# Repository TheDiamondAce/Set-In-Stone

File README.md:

# Set In Stone

# Motivation
Starting off with the motivation, I wanted to challenge myself, making something big for my second project, upon which I decided to ultilize my skills of CAD over 2 years on onshape and also my newfound knowledge of C++ hardware coding
I wanted to do a minigame of sorts, learning how modules work and interact with microcontrollers. I realized that most modules use a combination of using eletrical charges to output or input values into code. Which I found to be a revalation suprisingly

# What is this?
This project is a minigame similar to Simon Says and Bop it combined, you have to do multiple inputs to get a point, making it harder and harder as you progress. It is a reaction game of sorts, benefiting the people with great hand to eye coordination

# How to Build?
To build this, you first need to get the pieces as listed in the BOM, you will have to download the code from the Code folder and need to 3D print the enclosure/chassis as well as the button caps. Then, you will need to get the required modules and follow the wiring diagram as shown below here. For the PCB, you will need to first remoe the 3 wires on the left hand of the tft display since you wont need it for the build. Then after you remove it, you will need to solder the modules onto the PCB, however, the parts that you fit to the LID first are the joystick and the display. Then after you connect the PCB to the modules and also to the lid, you will need to get the usb c extension cable and fit it into the usb c gap in the bottom. After, its just a matter of plugging into a power source through the cable, then plug and play!
# What am I proud of?
Most definitely the code first, then the CAD, but not far behind. The reason for this is because I think for the first time, I actually understood the code sorta, and figured out what each thing does, actually using struct functions and enum functions, in an actual way. (Update) Okay, so the first thing I'm proud of now is the PCB as this is the first time i've ever done PCB tinkering, and I'm glad to say, it was a success!
Usually, when I coded, I never really bothered to use such types of functions, but with this project, I realized that, im getting better at coding. For CAD, I really am happy that I managed to get all of the constraints to a precises level to my standards. Also the way I designed it was 
sorta challenging for me at my level.
# What is the next steps?
Im thinking of making it so that there will be more audio and a spritesheet on the display with a mascot, being happy or mad whenever you get something right and wrong. Im also thinking of adding bluetooth audio so that I can implement a simon says mechanic, making it so that on certain cases, you dont press unless the stone says lmao, but not soul says haha.
# Anything else
Nah 
# Ur CAD Diagrams and Wiring?
Oh shoot yeah ur right
# CAD Pictures

## Isometric

## Front

## Back

## Side

# BOM
| Name                                                                                          | Description                                                                           | Quantity | Price  | Why                                                                                        | Link                                                                                                                                                                                                                                                                                                                                                                                                                                                                                                                                                                                                                                |
|-----------------------------------------------------------------------------------------------|---------------------------------------------------------------------------------------|----------|--------|--------------------------------------------------------------------------------------------|-------------------------------------------------------------------------------------------------------------------------------------------------------------------------------------------------------------------------------------------------------------------------------------------------------------------------------------------------------------------------------------------------------------------------------------------------------------------------------------------------------------------------------------------------------------------------------------------------------------------------------------|
| Joystick                                                                                      | A module that uses potentiometers and a stick to measure values                       | 1        | $8.79  | So you can do stuff to memorize for the minigame                                           | https://www.amazon.com/DKARDU-Dual-axis-Joystick-Control-Breakout/dp/B0B5GLYPLT/ref=sr_1_6_sspa?dib=eyJ2IjoiMSJ9.azZ62n4Tl8ZwkrheJyqyCndrP1SV71A4xyAr-iuhJYzian_VPAm1-wcJa1kETLtxM4eNGt-xxm1leb5CyeYzA3nBElRKq_MmfamtrXjfZvH7wPZkzrT96BrQEydKYWCSkKjlWEekTF7VWtR9tcMjoZKWhNFTWNypkJJN8fer6AzldJ-0Q4IYCG_6cRPB-GjUYue5LsoKmklUHP6XbxF4PJ9gZ4sy5qI4osEVQvxmUko.qd12qxOC_v7GZmm8GlitAnJ3g7_pRsO_EVmVD7kz0sU&dib_tag=se&keywords=KY-023&qid=1781695753&sr=8-6-spons&sp_csd=d2lkZ2V0TmFtZT1zcF9tdGY&psc=1                                                                                                                                |
| 12mm Button                                                                                   | A tactile switch that either connects a cirucuit or disconnects depending on input    | 4        | $12.07 | So you can click stuff to memorize for the minigame                                        | https://www.amazon.com/Uxcell-a11111400ux0132-Momentary-Tactile-Button/dp/B0090VQLDK                                                                                                                                                                                                                                                                                                                                                                                                                                                                                                                                                |
| 12mm Button Caps (Red Green Yellow Blue)                                                      | The caps to indentify which button is which (Will be 3D printer most likely)          | 4        | $0.00  | To know which button is which.                                                             | can 3D print through hackclub or by yourself                                                                                                                                                                                                                                                                                                                                                                                                                                                                                                                                                                                        |
| Potentiometer                                                                                 | A module that uses potentiometers and a stick to measure values through rotation      | 1        | $9.99  | Another cool function that gives varation and intresting mechanics                         | https://www.amazon.com/TWTADE-Adjustable-Potentiometer-Resistance-XH2-54-3P/dp/B082FCRQS2/ref=sr_1_11?dib=eyJ2IjoiMSJ9.TaTUlh95QswS_FIIMPYmhtrGpujREngP3Xc1oQRyB9rYfzo5Gjz4PTvWpn5iXK9dcDXyauCQyVTScgKtQiiCgd3LLyPBGxHL-tvGMzznu9_sFYWY9xP6C6awwAKLKjAjD54kWNmqUPUcvBHwoTWNZ5n1v20SmyDv5QPkhg_GJn26vWFLQ7iqdO7V3fx2rxiDINDQcKF5Hye8oN6JiOwa8UQbfrgA9xlyOhBGqnJD3KQ.hsZpGYPSabo9mENvFcCT4852xHdjX3BdothB3Qju_3g&dib_tag=se&keywords=potentiometer&qid=1781262502&sr=8-11&th=1                                                                                                                                                        |
| TFT LCD 2.4 inch ILI9341 Touch                                                                | Display used to show what inputs to press next and as well as score and timer         | 1        | $12.39 | To see what inputs to do next and other data                                               | https://www.amazon.com/ACEIRMC-ILI9341-Display-Touch-240X320/dp/B0C4D5S6G5/ref=sr_1_10_sspa?crid=1KKGFFL8GGC72&dib=eyJ2IjoiMSJ9.aNbS-hCnwROiq-lihDWLj0bSTkExzZcUEg9Thz-MRRtS2XSDTZusdgq0aD1F0WmFP2z1icua7XtMO6m0dMOpn8SqrOFp1HIlcN4kiqw6-RlV7hZO4ruwCns7e_xrwwarWxaiSyrChwiIRUrUY_RlX9OKgmKKALx-gO4lSBbiMaZfKv6a7KsmvzFghX94ueB0tjP9qSX40MXT01v37X8MMYSJqIt6UnkreQ59ftwFdiegDUDVujNbTPq7P3rk02P9OOVeiCEMzoFH8qXlYbO1NNMZsi5VeRhwTNT7sHwGj98.L9Ilfuyvs66CsTIbDNYf3OsazpswS6k4iaS05y2B6dk&dib_tag=se&keywords=ili9341&qid=1781262418&s=electronics&sprefix=ili%2Celectronics%2C409&sr=1-10-spons&sp_csd=d2lkZ2V0TmFtZT1zcF9tdGY&psc=1 |
| -ESP 32                                                                                       | The Microcontroller that will control all functions of the minigame as well as logic. | 1        | $9.99  | To control the whole minigame and logic                                                    | http://amazon.com/HiLetgo-ESP-WROOM-32-Development-Microcontroller-Integrated/dp/B0718T232Z/ref=sr_1_3?crid=1USIEYMJJ17B2&dib=eyJ2IjoiMSJ9.qMJJKscaTbDZH8KOrPXaSvvBOSev_9dSPToXjxjL2hvyn1gBn6UPJN0hkgfCA46MeGIMW0m_k8uVP6ohS8y2Ybx0WAhwI7WeRI7HGIEx1FzRCBDUpYc9OEv48KKiBbsEpRw-msTD6rmtDv4Xvt-FdBguBvBYlMMj4hzZRICsg1IFudiHZVD_F8MFEsmYWqc5av-fzu7UHVx2QYcllMYcUQXPrnJ9yVsP_ArNuaKStI0.KplrsOIrBP554ZSAFR6EYMaRAuKfkU4c-5f2bEqIvqA&dib_tag=se&keywords=esp32&qid=1781262965&sprefix=esp%2Caps%2C477&sr=8-3&th=1                                                                                                                     |
| Half Breadboard                                                                               | A module used to have extra ports and have more leeway in circuit connections         | 1        | $5.99  | For extra ports to connect GND and PWR and other wires too.                                | https://www.amazon.com/WWZMDiB-SYB-170-Breadboard-Plates-Multicolored/dp/B09YXQJMTG/ref=sr_1_3?crid=2AKGMD1N41ZHO&dib=eyJ2IjoiMSJ9.EQvCK09g_r0CejNbKABqFdsxqhs5KyJ1I0W1Q395qgARL8M_eCKhoj9mKheDOgAb_PUbl3fS3TNz_-PkcA5Ur8CU2_LE8D1_eW4bH6tGqQ7fgX-P_ELVVSjGnskkUdkdZKxuxYHAbqnzcsl53FGLHvlJk3CfdosCvz8g7-GZr3ywx0Ic_oW_dglX5jAHgBxu-roh24M2mq6ot_Jl_-sd2wQRqCW9XuF1Zhf4ILJQ5lI.RYnkEh1qahxXQ1VyEr87oe8Coe7Rg22-y_Lfwkx4oYs&dib_tag=se&keywords=half+breadboard&qid=1781695848&sprefix=half+breadboard%2Caps%2C403&sr=8-3                                                                                                            |
| Dupont Female-Male Wires                                                                      | Used to connect modules to microcontroller and circuits.                              | ~40      | $6.99  | Bruh, so the whole thing can get some electricity.                                         | https://www.amazon.com/Solderless-Multicolored-Electronic-Breadboard-Protoboard/dp/B09FPJM3L9?th=1                                                                                                                                                                                                                                                                                                                                                                                                                                                                                                                                  |
| 3D Printer Enclousure.                                                                        | The host for all modules necessary in the build                                       | 1        | $0.00  | To put all of the modules into one area                                                    | can print through hackclub or by yourself with step file                                                                                                                                                                                                                                                                                                                                                                                                                                                                                                                                                                            |
| M7 Jam Nut                                                                                    | 7mm in diameter Jam nut. (Optional because potentiometer has this.)                   | 1        | $0.00  | To Screw in the Potentiometer                                                              | not necessary since potentiometer link has the jam nut already                                                                                                                                                                                                                                                                                                                                                                                                                                                                                                                                                                      |
| M4 Screw                                                                                      | 4mm in diameter Screw                                                                 | 4        | $9.99  | To Screw in the Joystick Module and display.                                               | https://www.amazon.com/mxuteuk-450PCS-Screws-Assortment-Socket/dp/B0CS67BLQJ/ref=sr_1_3?crid=1H3GBSELCRPJT&dib=eyJ2IjoiMSJ9.WS2IYPVxCSdSo7wd5Ro8qswOwSorxoGo4OOJvZ9bUqPprJ30Ccqh94VnURS4gSkMOYPS-ZEDVI7dUfj0_-NAmAo7UKL2-5WZ9QllNB-5f-a9xEkRlvXgIX7IboPFqkcX9JXqOVSzvbsQEum2MjjYmuCvdaien_4XW7I09f5VQ7svLen--Tr_Kp-oOPXzIEYotNzGKD5c1CMrQCy695_CdF8zfiQV0dCKJ3mnVq9N8lY.zClPtqKY4btAdvUcQPcIhxSYIAlmEpf7oDnjbVvqnpU&dib_tag=se&keywords=m3%2Band%2Bm4%2Bjam%2Bnut%2Band%2Bscrews&qid=1781696093&sprefix=m3%2Band%2Bmjam%2Bnut%2Band%2Bscrews%2Caps%2C394&sr=8-3&th=1                                                                |
| M4 Jam Nut                                                                                    | 4mm in diameter Jam Nut                                                               | 4        | $0.00  | ~. ~. ~. ~                                                                                 | ~~~ (the link above has both the jam nut and screws)                                                                                                                                                                                                                                                                                                                                                                                                                                                                                                                                                                                |
| M3 Screw                                                                                      | 3mm in diameter Screw for Electronics                                                 | 4        | $0.00  | For PCB                                                                                    | ~~~ (the link above has both the jam nut and screws)                                                                                                                                                                                                                                                                                                                                                                                                                                                                                                                                                                                |
| M3 Jam Nut                                                                                    | To tighten the 3mm screw                                                              | 4        | $0.00  | For PCB                                                                                    | ~~~ (the link above has both the jam nut and screws)                                                                                                                                                                                                                                                                                                                                                                                                                                                                                                                                                                                |
| PCB                                                                                           | A electrical component custom made for a specific task                                | 1        | $62.32 | So the whole thing can be connected seamlessly if not using a breadboard and jumper wires. | https://www.pcbway.com/orderonline.aspx?outsideid=4bd99289-acd0-49fe-ba78-ffb373cdaed3                                                                                                                                                                                                                                                                                                                                                                                                                                                                                                                                              |
| THE LINKS USED MIGHT HAVE MULTIPLE PIECES SINCE THEY ARE THE BEST BANG FOR BUCK ON AMAZON.*** |                                                                                       |          |        |                                                                                            |                                                                                                                                                                                                                                                                                                                                                                                                                                                                                                                                                                                                                                     |
|                                                                                               | TOTAL PRICE=                                                                          | $138.52  |        |                                                                                            |                                                                                                                                                                                                                                                                                                                                                                                                                                                                                                                                                                                                                                     |
|                                                                                               | (MINUS $5.99 if using breadboard and $62.32 IF USING BREADBOARD!!)                    |          |        |                                                                                            |                                                                                                                                                                                                                                                                                                                                                                                                                                                                                                                                                                                                                                     |

# Wiring Diagram

## Breadboard Prototype Wiring

## Schematics PCB Diagram

## PCB Footprint Diagaram

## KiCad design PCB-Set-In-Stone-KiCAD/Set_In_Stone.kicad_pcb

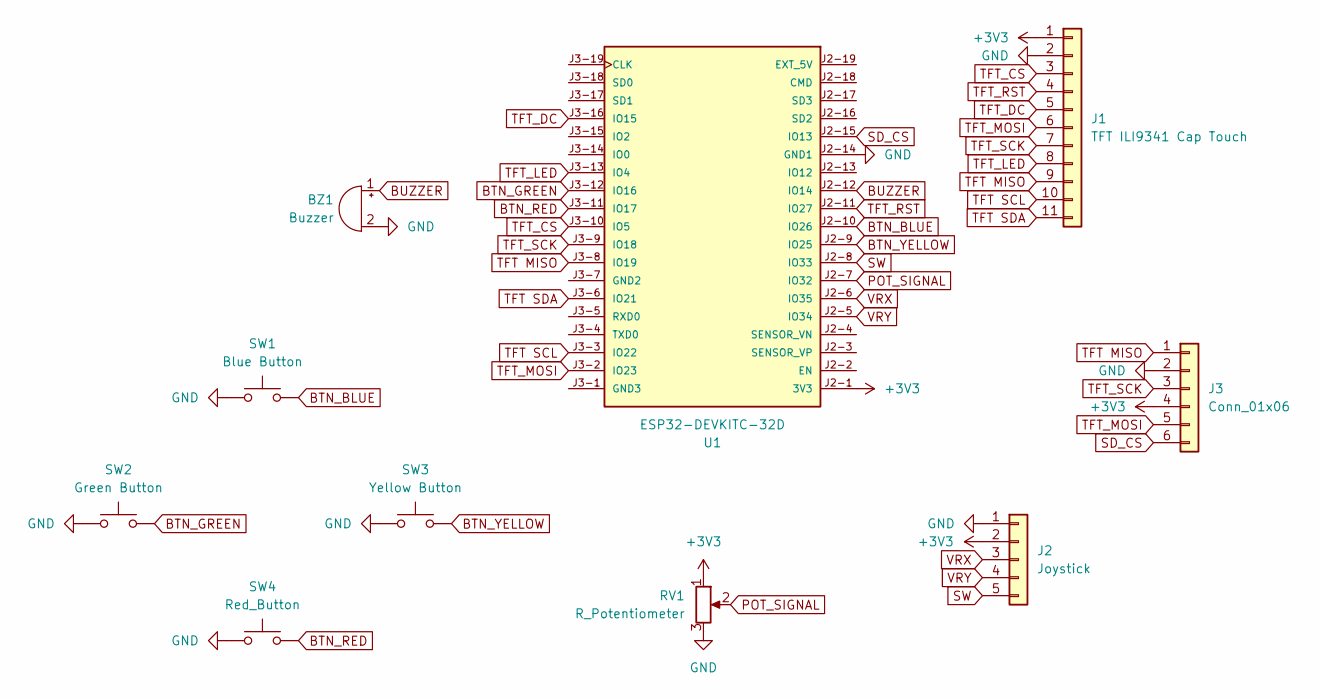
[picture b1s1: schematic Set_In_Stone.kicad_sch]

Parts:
BZ1: Buzzer; Buzzer_12x9.5RM7.6
J1: TFT ILI9341 Cap Touch; PinHeader_1x11_P2.54mm_Vertical
J2: Joystick; PinSocket_1x05_P2.54mm_Vertical
J3: Conn_01x06; PinSocket_1x06_P2.54mm_Vertical
RV1: R_Potentiometer; PinSocket_1x03_P2.54mm_Vertical
SW1: Blue Button; SW_PUSH-12mm
SW2: Green Button; SW_PUSH-12mm
SW3: Yellow Button; SW_PUSH-12mm
SW4: Red_Button; SW_PUSH-12mm
U1: ESP32-DEVKITC-32D; MODULE_ESP32-DEVKITC-32D; PARTREV V4

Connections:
+3V3: J1.1, J2.2, J3.4, RV1.1, U1.J2-1 (3V3)
BTN_BLUE: SW1.2, U1.J2-10 (IO26)
BTN_GREEN: SW2.2, U1.J3-12 (IO16)
BTN_RED: SW4.2, U1.J3-11 (IO17)
BTN_YELLOW: SW3.2, U1.J2-9 (IO25)
BUZZER: BZ1.1 (+), U1.J2-12 (IO14)
GND: BZ1.2 (-), J1.2, J2.1, J3.2, RV1.3, SW1.1, SW2.1, SW3.1, SW4.1, U1.J2-14 (GND1)
POT_SIGNAL: RV1.2, U1.J2-7 (IO32)
SD_CS: J3.6, U1.J2-15 (IO13)
SW: J2.5, U1.J2-8 (IO33)
TFT MISO: J1.9, J3.1, U1.J3-8 (IO19)
TFT SCL: J1.10, U1.J3-3 (IO22)
TFT SDA: J1.11, U1.J3-6 (IO21)
TFT_CS: J1.3, U1.J3-10 (IO5)
TFT_DC: J1.5, U1.J3-16 (IO15)
TFT_LED: J1.8, U1.J3-13 (IO4)
TFT_MOSI: J1.6, J3.5, U1.J3-2 (IO23)
TFT_RST: J1.4, U1.J2-11 (IO27)
TFT_SCK: J1.7, J3.3, U1.J3-9 (IO18)
VRX: J2.3, U1.J2-6 (IO35)
VRY: J2.4, U1.J2-5 (IO34)

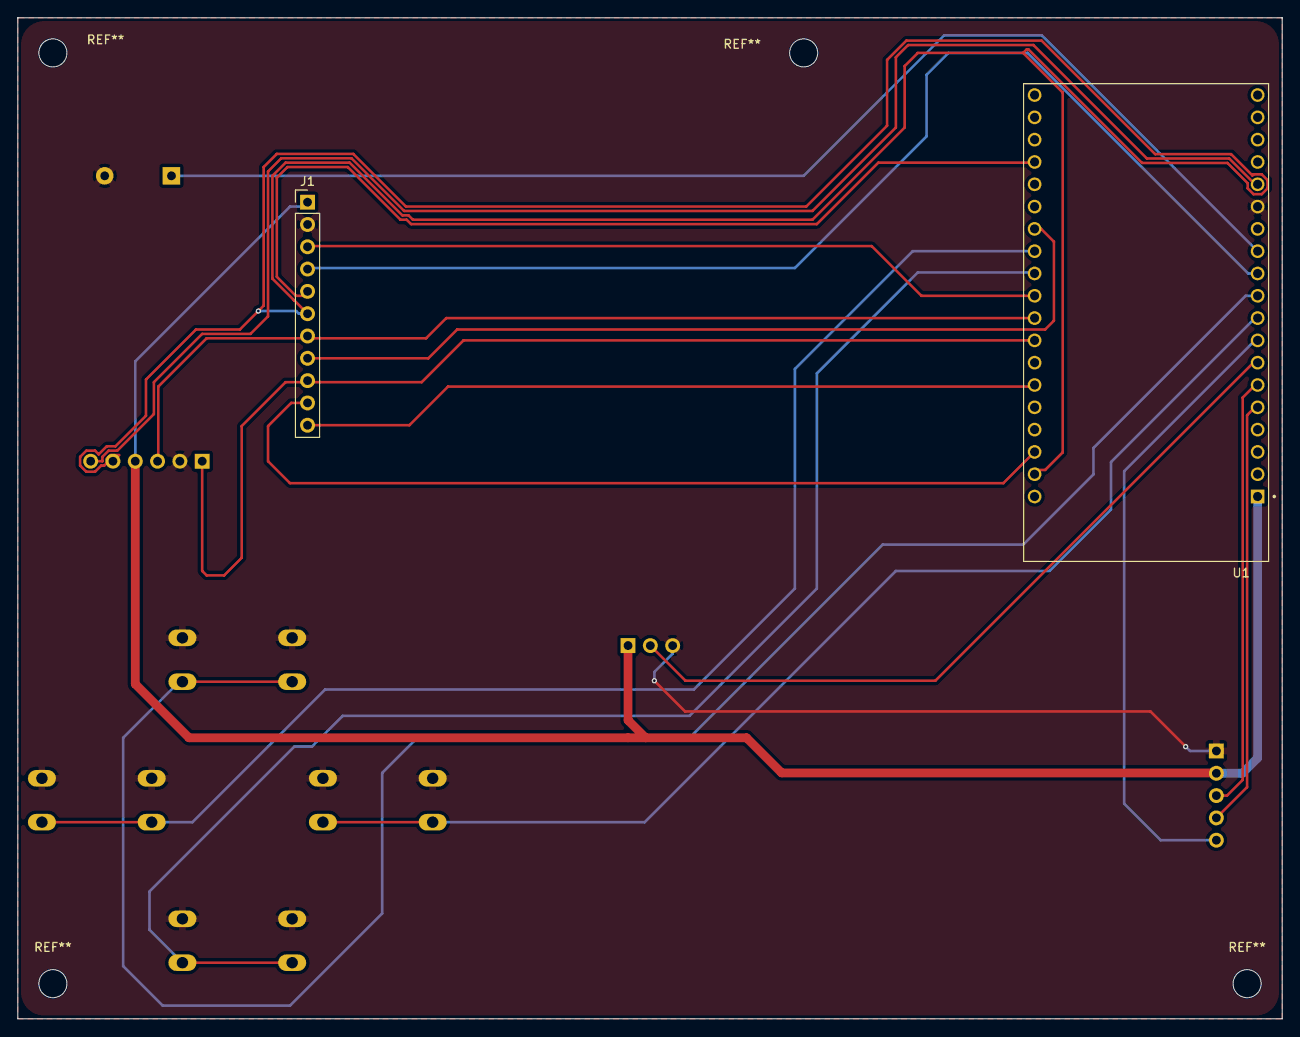
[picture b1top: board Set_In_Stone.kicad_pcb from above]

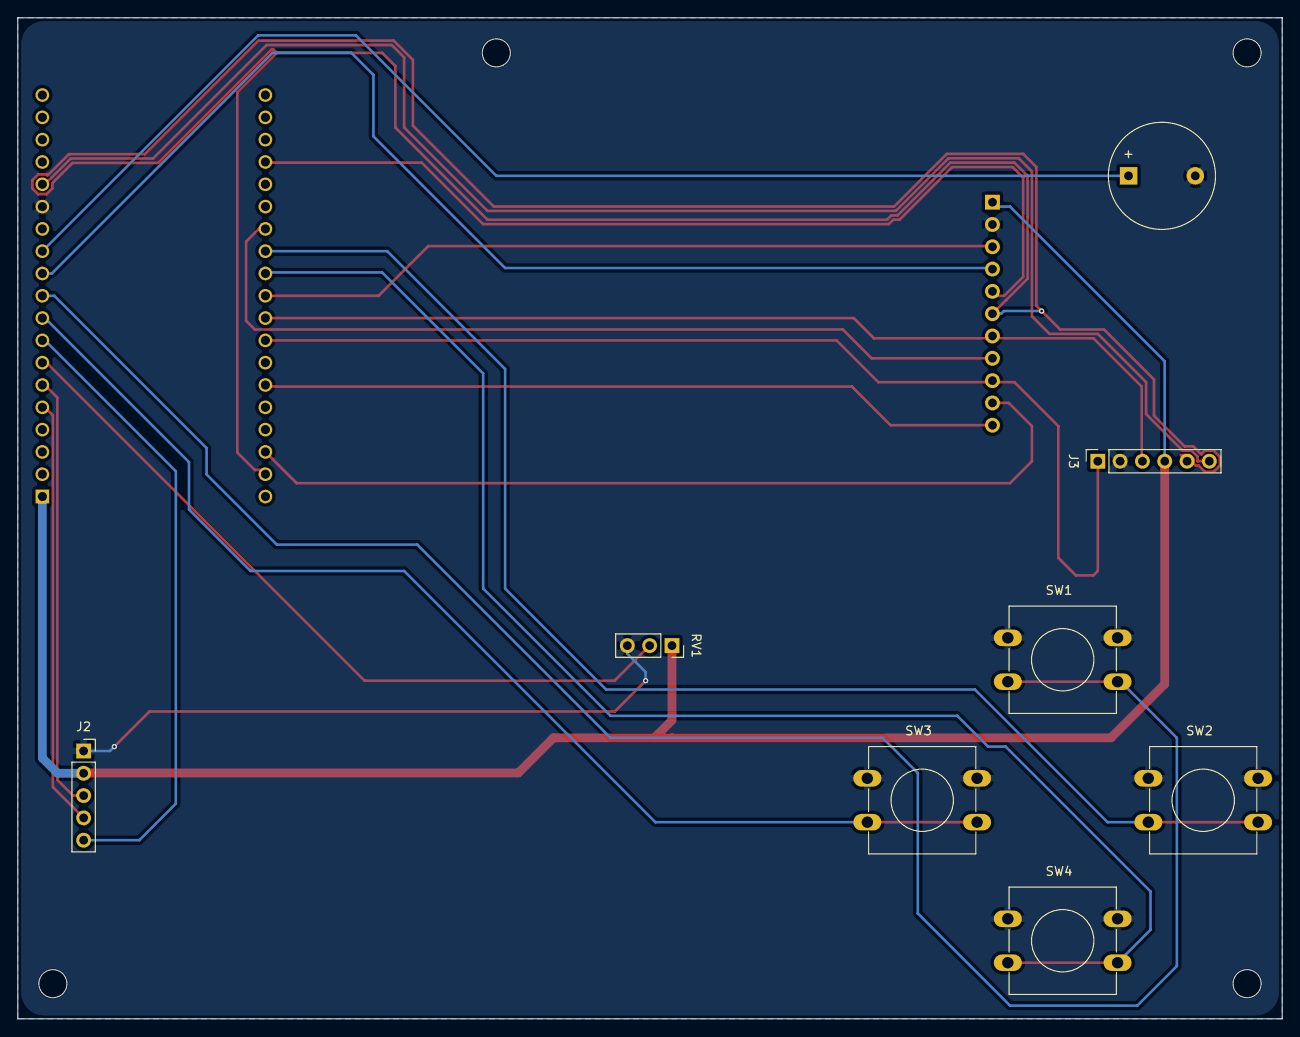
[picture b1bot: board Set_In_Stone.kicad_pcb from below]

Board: 2 copper layers, 144.0 x 114.0 mm, 10 parts (8 on the bottom side), 21 nets.

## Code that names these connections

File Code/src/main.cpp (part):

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#define BUTTONYELLOW 25

//Buzzer Ports Defintion
#define BUZZER 15

//Display Ports Defintion
#define CS 5
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#define SDA 21

//Joystick Ports Defintion
#define VRX 35
#define VRY 34
#define SW 33

//Potentiometer Ports Definition
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    pinMode(BUTTONGREEN, INPUT_PULLUP);
    pinMode(BUTTONBLUE, INPUT_PULLUP);
    pinMode(BUTTONYELLOW, INPUT_PULLUP);
    pinMode(VRX, INPUT);
    pinMode(VRY, INPUT);
    pinMode(SW, INPUT_PULLUP);
    pinMode(POT, INPUT);
    pinMode(BUZZER, OUTPUT);
    
    pinMode(LED, OUTPUT);
    digitalWrite(LED, HIGH);
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
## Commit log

2026-06-09 made foundational prototype of Set In Stone
    I got the main.cpp file as well as the wiring diagram from wokwi to consider this a first polished prototype of Set In Stone.
2026-06-10 Added Difficulty Menu To Minigame
    In this update, I added a difficulty bar which allows you to select easy medium hard, which will affect the timer limit.
2026-06-10 version with buzz() and potentiometer visually made by me
2026-06-12 Organizing and Adding Final Stuff
    In this update, i have included the CAD Folder, put the code in a dedicated folder, and added the zine and the wiring diagram.
2026-06-12 Add Onshape link to OnshapeLink.txt
2026-06-12 Update README with build instructions for minigame
    Added a section on how to build the minigame, detailing required pieces and assembly instructions.
2026-06-13 Made PCB of Set In Stone
    In this update I decided to make the set in stone PCB as I realized this is a pretty complex project so why not make it more complex to get burnout pathway lmao. Jokes aside, proud of my first PCB ev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
2026-06-13 Made finishing touches to PCB
    In this update, I made the final touches for the PCB of the Set In Stone project.
2026-06-13 Update README with new wiring and PCB diagrams
    Added new sections for breadboard prototype wiring, schematics PCB diagram, and PCB footprint diagram.
2026-06-13 Updated BOM
    Added PCB and M3 Screw Components to the BOM list
2026-06-17 Updated B.O.M and added high quality PDF
    This update is to revise my project so that I can get it approved, I have made it so that there are links for the people who want to rebuild my project from scratch and also a pdf of the zine so that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
2026-06-17 Added gitingore for kicad
2026-06-17 Made Wires Bigger and Made PCBWAY GERBER FILES
    In this update, I redid the routing for the wires slightly so that there isnt redudant wires hopefully as well as increase the wire thickness for the general wiring as well as for the VCC which is th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
2026-06-17 Add new images to README for PCB diagrams
    Added new images for PCB schematics and footprint diagrams.
2026-06-17 Added Redesigned CAD and also PCB
    In this update I added the CAD and PCB files for the project Set In Stone. I will now turn my project in for review
2026-06-21 Added QR Code to Zine
2026-06-21 Update image and fix typos in README
    Updated image in README and corrected typos in the text.
2026-06-23 Update Set In Stone zine assets and .DS_Store
    Replace Set In Stone Zine PDF and PNG with updated versions. Refresh .DS_Store files in PCB-Set-In-Stone-KiCAD and PCBWayGerberFilesandPlotFiles directories (macOS Finder metadata changes).
2026-06-28 Fixed bugs need to be adressed
    In this update, you know whats up.
